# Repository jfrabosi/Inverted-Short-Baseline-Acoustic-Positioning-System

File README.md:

# Introduction
This is the codebase for my Master's thesis in Mechanical Engineering. For this project, I developed:
- A four-stacked hexapod platform, with each platform capable of independent control, used as a ground-truth positioning system
- An ultrasonic, air-based positioning system consisting of four receivers (with active band-pass filtering) and a transmitter
- A method for transmitting 2kb/s of data over ultrasonic sound
- And much more!

My thesis is available at [Cal Poly's Digital Commons](https://digitalcommons.calpoly.edu/theses/2914/) and on my [LinkedIn profile](https://www.linkedin.com/in/jakobhadal/). You can see a [video of the system in action here](https://www.youtube.com/watch?v=QgJyHS0l2EE).

The hardware used includes an ESP32-WROOM (hexapod platform), STM32H723 (acoustic positioning algorithm and sensor fusion), and STM32F411 (acoustic transmitter). The ESP32 was programmed using PlatformIO and C++, and the STM32s were programmed using STM32CubeIDE and C. Some data analysis was performed using Python.

# Abstract
This document details the design, implementation, testing, and analysis of an inverted short baseline acoustic positioning system. The system presented here is an above-water, air-based prototype for an underwater acoustic positioning system; it is designed to determine the position of remotely-operated underwater vehicles (ROVs) and autonomous underwater vehicles (AUVs) in the global frame using a method that does not drift over time.
		
A ground-truth positioning system is constructed using a stacked hexapod platform actuator, which mimics the motion of an AUV and provides the true position of an ultrasonic microphone array. An ultrasonic transmitter sends a pulse of sound towards the array; microphones on the array record the pulse of sound and use the time shift between the microphone signals to determine the position of the transmitter relative to the receiver array. The orientation of the array, which is necessary to transform the position estimate to the global frame, is calculated using a Madgwick filter and data from a MEMS IMU. Additionally, a dead reckoning change-in-position estimate is formed using the IMU data. The acoustic position estimate is combined with the dead reckoning estimate using a Kalman filter. The accuracy of this filtered position estimate was verified to 22.1mm within a range of 3.88m in this air-based implementation. The ground-truth positioning system runs on an ESP32 microcontroller using code written in C++, and the acoustic positioning system runs on two STM32 microcontrollers using code written in C.
		  
Extrapolation of these results to the underwater regime, as well as recommendations for improving upon this work, are included at the end of the document. All code written for this thesis is available on GitHub and is open-source and well-documented.

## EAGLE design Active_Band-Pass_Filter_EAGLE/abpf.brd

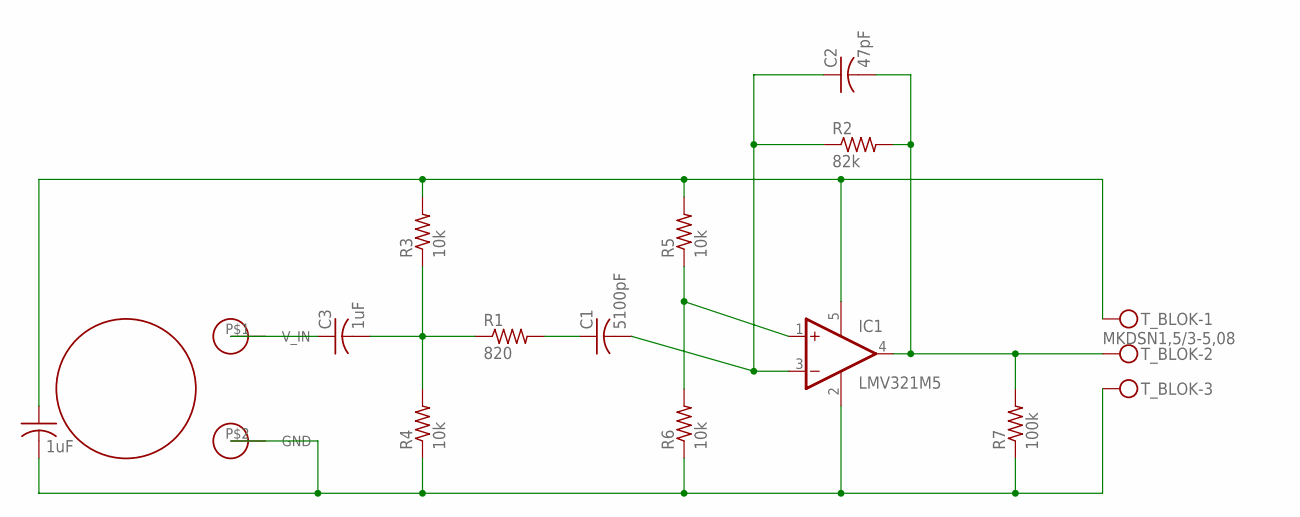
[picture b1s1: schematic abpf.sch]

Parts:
C1: 5100pF; C0805
C2: 47pF; C0805
C3, C4: 1uF; C0805
IC1: LMV321M5; SOT23-5
R1: 820; R0805
R2: 82k; R0805
R3, R4, R5, R6: 10k; R0805
R7: 100k; R0805
T_BLOK: MKDSN1,5/3-5,08
U$1: 10MM_USONIC

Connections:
GND: C4.2, IC1.2 (V-), R4.1, R6.1, R7.1, T_BLOK.3, U$1.P$2 (GND)
unnamed: C3.2, R1.1, R3.1, R4.2
unnamed: C1.1, R1.2
unnamed: IC1.1 (+IN), R5.1, R6.2
unnamed: C2.2, IC1.4 (OUT), R2.2, R7.2, T_BLOK.2
unnamed: C4.1, IC1.5 (V+), R3.2, R5.2, T_BLOK.1
unnamed: C3.1, U$1.P$1 (V_IN)
unnamed: C1.2, C2.1, IC1.3 (-IN), R2.1

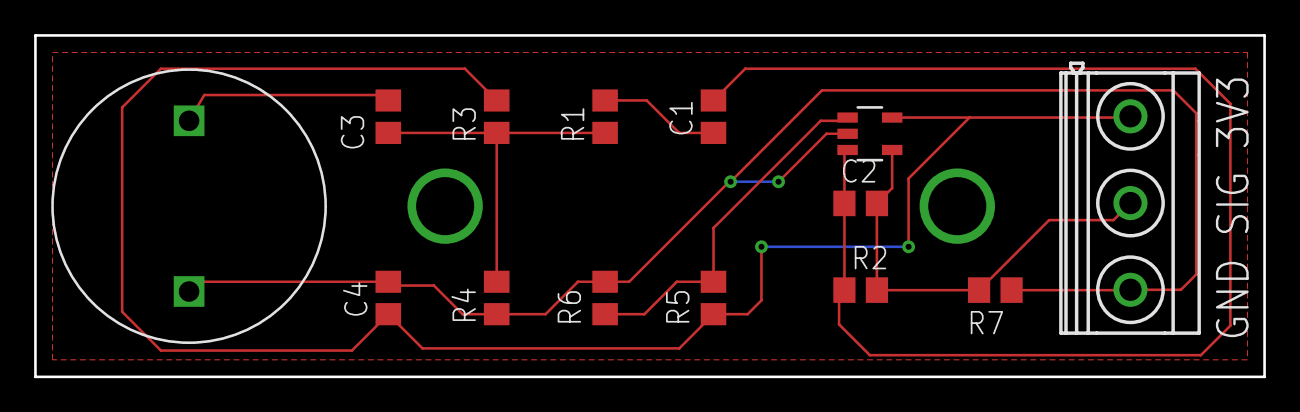
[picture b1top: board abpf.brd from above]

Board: 2 copper layers, 72.0 x 20.0 mm, 14 parts (0 on the bottom side), 8 nets.

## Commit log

2024-08-11 Added ESP32 Fo-SHIP positoner code
2024-08-16 added ABF Eagle files
2024-08-18 Added transmitter and receiver code
2024-08-18 Added transmitter and receiver code (STM32)
2024-08-22 updated receiver code (mainly comments)
2024-08-29 ppt v0.1
2024-09-06 Added CAD files and raw test data
2024-09-06 Uploaded thesis chapters
